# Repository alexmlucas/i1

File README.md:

# i1
An accessible motion based guitar instrument

This project is part of PhD Research being undertaken by Queens University Belfast. 

i1 is a bespoke instrument designed for and with a musician with a physical disability. The intial concept is for the musician to use head and arm movement to trigger playback of chords on a virtual guitar.

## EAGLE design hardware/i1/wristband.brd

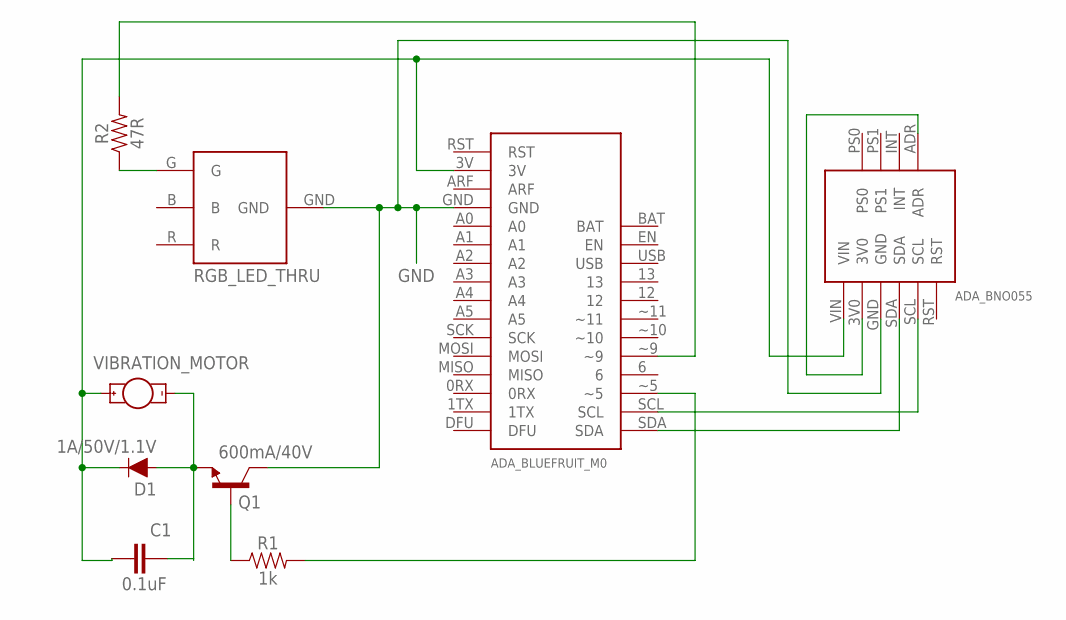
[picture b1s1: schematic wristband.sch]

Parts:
BF1: ADA_BLUEFRUIT_M0
BNO1: ADA_BNO055
C1: 0.1uF; CAP-PTH-SMALL-KIT
D1: 1A/50V/1.1V; DIODE-1N4001
Q1: 600mA/40V; TO-92
R1: 1k; AXIAL-0.3
R2: 47R; AXIAL-0.3
RGB_LED1: RGB_LED_THRU; RGB_LEB_RGB_2
U$1: VIBRATION_MOTOR

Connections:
GND: BF1.GND, BNO1.GND, Q1.1 (C), RGB_LED1.GND
unnamed: BF1.SDA, BNO1.SDA
unnamed: BF1.SCL, BNO1.SCL
unnamed: BF1.3V, BNO1.VIN, C1.1, D1.C, U$1.+
unnamed: BNO1.3V0, BNO1.ADR
unnamed: R2.P$1 (1), RGB_LED1.G
unnamed: BF1.~9, R2.P$2 (2)
unnamed: C1.2, D1.A, Q1.3 (E), U$1.-
unnamed: Q1.2 (B), R1.P$1 (1)
unnamed: BF1.~5, R1.P$2 (2)

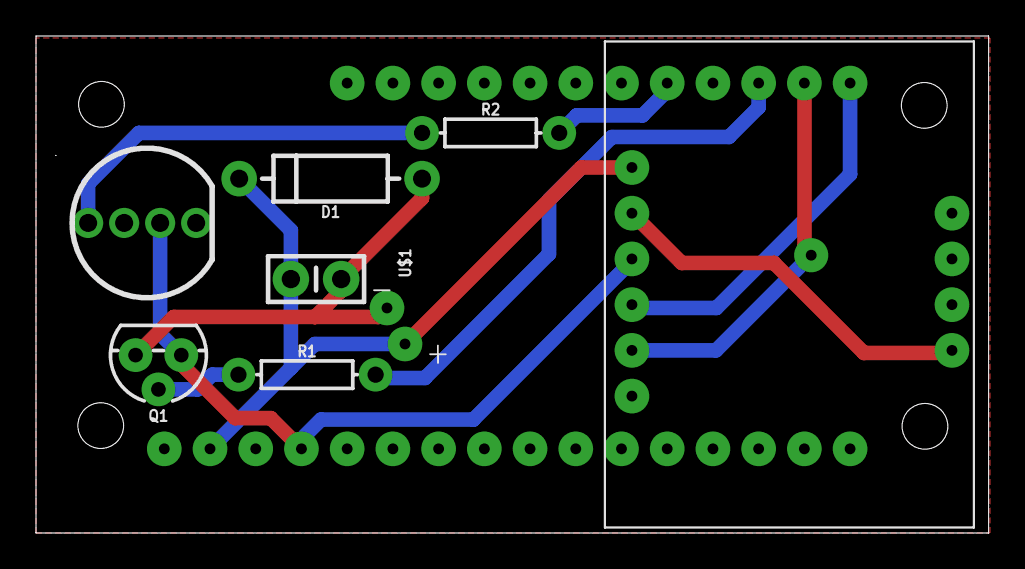
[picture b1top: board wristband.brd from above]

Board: 2 copper layers, 52.9 x 27.6 mm, 9 parts (0 on the bottom side), 10 nets.

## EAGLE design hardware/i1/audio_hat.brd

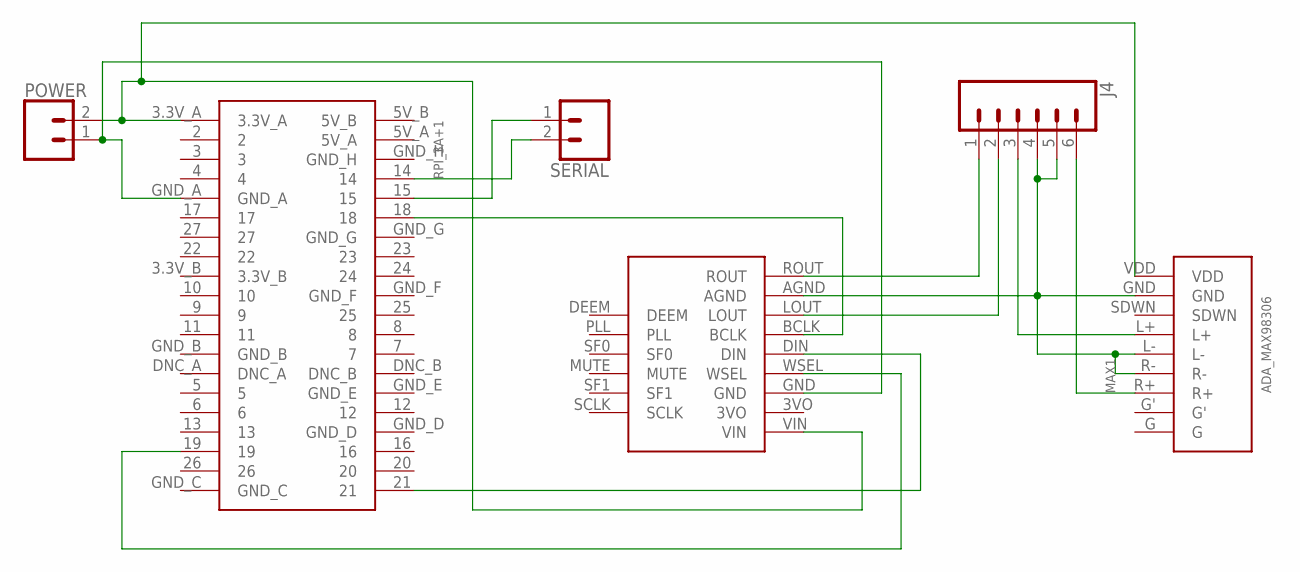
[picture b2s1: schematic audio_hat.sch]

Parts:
J4: CONN_06NO_SILK_NO_POP; 1X06_NO_SILK
MAX1: ADA_MAX98306
POWER: CONN_02; 1X02
RPI_3A+1: RPI_3A+
SERIAL: CONN_02; 1X02
UDA1: ADA_UDA1334

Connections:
unnamed: RPI_3A+1.19, UDA1.WSEL
unnamed: POWER.1, RPI_3A+1.GND_A, UDA1.GND
unnamed: MAX1.VDD, POWER.2, RPI_3A+1.3.3V_A, UDA1.VIN
unnamed: RPI_3A+1.21, UDA1.DIN
unnamed: J4.1, UDA1.ROUT
unnamed: J4.2, UDA1.LOUT
unnamed: J4.4, J4.5, MAX1.GND, MAX1.L-, MAX1.R-, UDA1.AGND
unnamed: J4.3, MAX1.L+
unnamed: RPI_3A+1.14, SERIAL.2
unnamed: J4.6, MAX1.R+
unnamed: RPI_3A+1.15, SERIAL.1
unnamed: RPI_3A+1.18, UDA1.BCLK

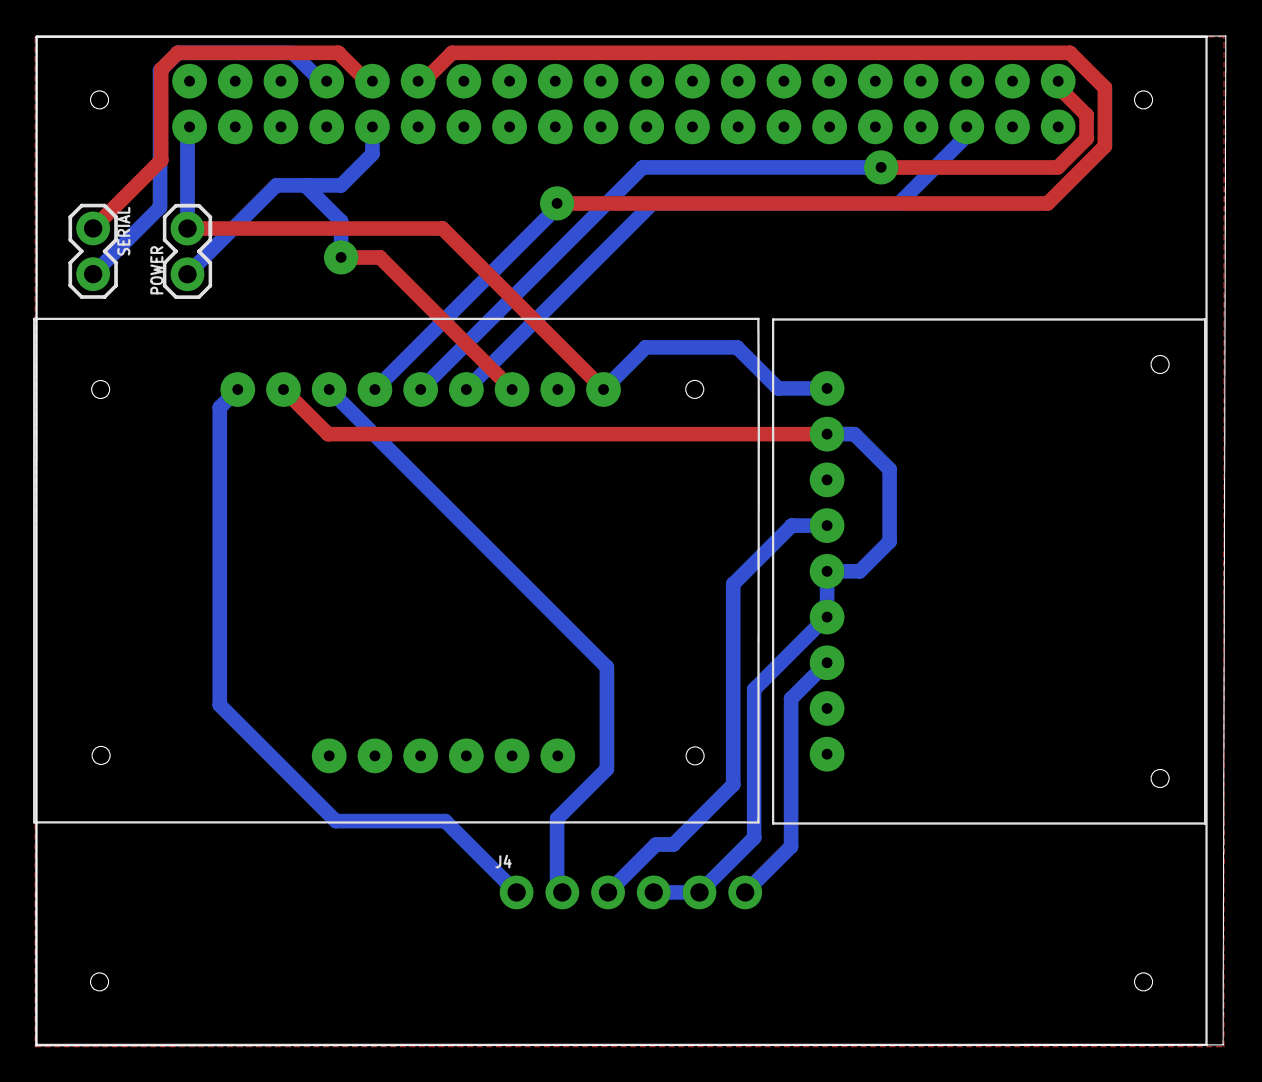
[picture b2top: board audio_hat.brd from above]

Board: 2 copper layers, 66.1 x 56.1 mm, 6 parts (0 on the bottom side), 12 nets.

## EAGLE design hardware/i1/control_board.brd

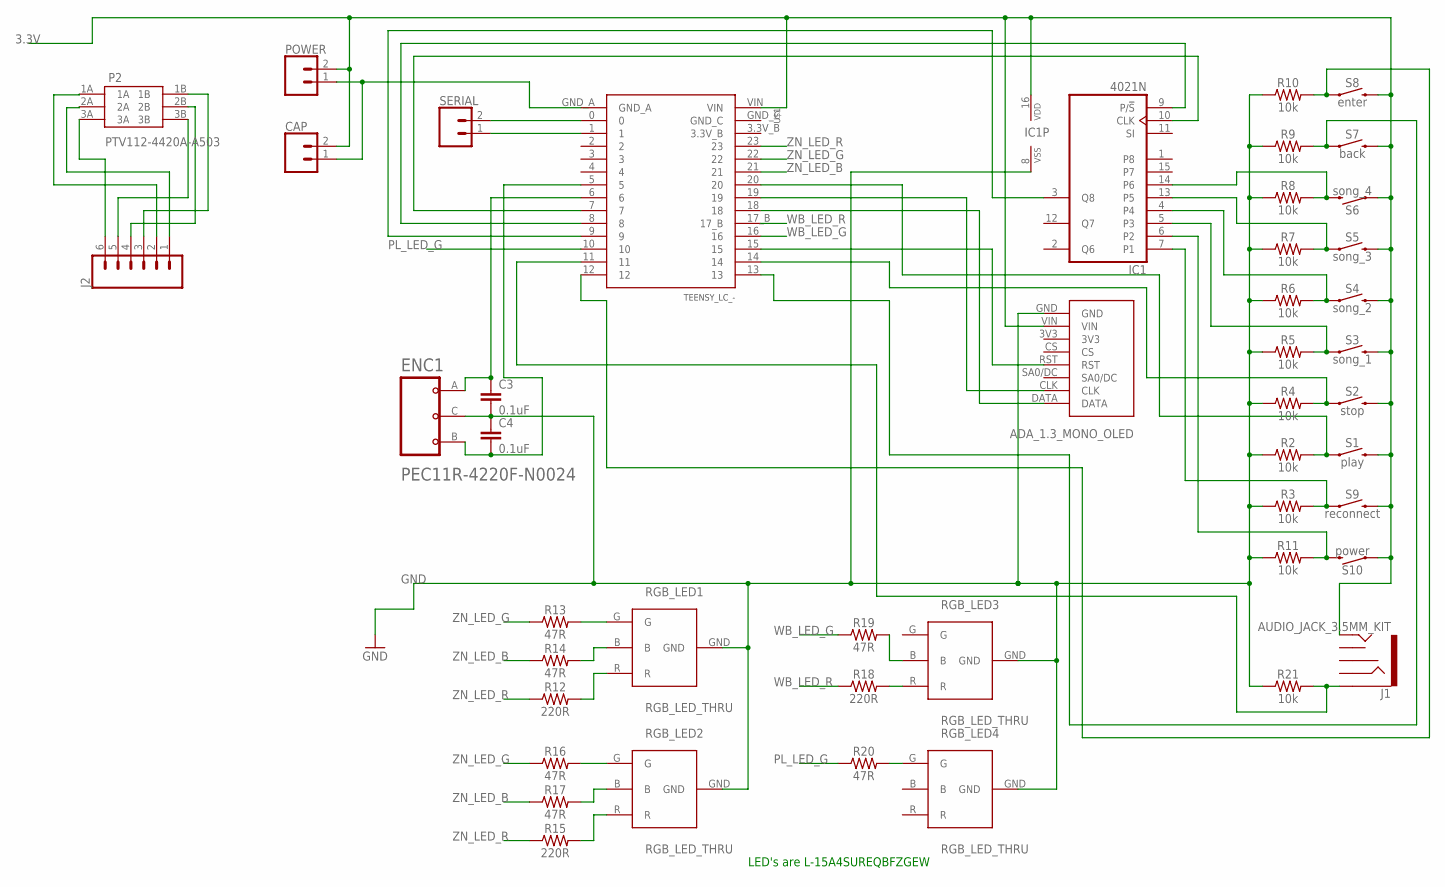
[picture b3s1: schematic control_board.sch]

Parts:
C3, C4: 0.1uF; CAP-PTH-SMALL-KIT
CAP: CONN_02; 1X02
ENC1: PEC11R-4220F-N0024
IC1: 4021N; DIL16
J1: AUDIO_JACK_3.5MM_KIT; AUDIO-JACK-KIT
J2: CONN_06NO_SILK_NO_POP; 1X06_NO_SILK
OLED1: ADA_1.3_MONO_OLED
P2: PTV112-4420A-A503; PTV122-4420A-A503
POWER: CONN_02; 1X02
R2, R3, R4, R5, R6, R7, R8, R9, R10, R11, R21: 10k; AXIAL-0.3
R12, R15, R18: 220R; AXIAL-0.3
R13, R14, R16, R17, R19, R20: 47R; AXIAL-0.3
RGB_LED1, RGB_LED2, RGB_LED3, RGB_LED4: RGB_LED_THRU; RGB_LEB_RGB_2
S1: play; TACTILE_SWITCH_PTH_6.0MM
S2: stop; TACTILE_SWITCH_PTH_6.0MM
S3: song_1; TACTILE_SWITCH_PTH_6.0MM
S4: song_2; TACTILE_SWITCH_PTH_6.0MM
S5: song_3; TACTILE_SWITCH_PTH_6.0MM
S6: song_4; TACTILE_SWITCH_PTH_6.0MM
S7: back; TACTILE_SWITCH_PTH_6.0MM
S8: enter; TACTILE_SWITCH_PTH_6.0MM
S9: reconnect; TACTILE_SWITCH_PTH_6.0MM
S10: power; TACTILE_SWITCH_PTH_6.0MM
SERIAL: CONN_02; 1X02
U$1: TEENSY_LC_-

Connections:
3.3V: CAP.2, IC1.16 (VDD), J1.TIP, OLED1.VIN, POWER.2, S1.3 (2), S2.3 (2), S3.3 (2), S4.3 (2), S5.3 (2), S6.1, S7.3 (2), S8.3 (2), S9.3 (2), S10.1, U$1.VIN
GND: C3.2, C4.1, CAP.1, ENC1.C (COMMON), IC1.8 (VSS), OLED1.GND, POWER.1, R2.P$1 (1), R3.P$1 (1), R4.P$1 (1), R5.P$1 (1), R6.P$1 (1), R7.P$1 (1), R8.P$1 (1), R9.P$1 (1), R10.P$1 (1), R11.P$1 (1), R21.P$1 (1), RGB_LED1.GND, RGB_LED2.GND, RGB_LED3.GND, RGB_LED4.GND, U$1.GND_A
unnamed: IC1.3 (Q8), U$1.9
unnamed: R13.P$2 (2), RGB_LED1.G
unnamed: R14.P$2 (2), RGB_LED1.B
unnamed: IC1.10 (CLK), U$1.7
unnamed: R12.P$2 (2), RGB_LED1.R
unnamed: R16.P$2 (2), RGB_LED2.G
unnamed: R17.P$2 (2), RGB_LED2.B
unnamed: IC1.9 (P/!S), U$1.8
unnamed: OLED1.DATA, U$1.18
unnamed: R4.P$2 (2), S2.1, U$1.14
unnamed: R9.P$2 (2), S7.1, U$1.13
unnamed: IC1.5 (P3), R5.P$2 (2), S3.1
unnamed: IC1.4, R6.P$2 (2), S4.1
unnamed: J1.SLEEVE, R21.P$2 (2), U$1.11
unnamed: IC1.13 (P5), R7.P$2 (2), S5.1
unnamed: IC1.14 (P6), R8.P$2 (2), S6.3 (2)
unnamed: SERIAL.1, U$1.1
unnamed: R10.P$2 (2), S8.1, U$1.12
unnamed: C3.1, ENC1.A (CHANNEL_A), U$1.6
unnamed: C4.2, ENC1.B (COMMON_B), U$1.5
unnamed: IC1.7 (P1), R3.P$2 (2), S9.1
unnamed: IC1.6 (P2), R11.P$2 (2), S10.3 (2)
unnamed: R15.P$2 (2), RGB_LED2.R
unnamed: R19.P$2 (2), RGB_LED3.B
unnamed: R18.P$2 (2), RGB_LED3.R
unnamed: R20.P$2 (2), RGB_LED4.G
unnamed: R2.P$2 (2), S1.1, U$1.20
unnamed: SERIAL.2, U$1.0
unnamed: J2.2, P2.1A
unnamed: OLED1.CLK, U$1.19
unnamed: OLED1.RST, U$1.15
unnamed: J2.1, P2.2A
unnamed: J2.6, P2.3A
unnamed: J2.4, P2.2B
unnamed: J2.5, P2.3B
unnamed: J2.3, P2.1B
PL_LED_G: R20.P$1 (1), U$1.10
WB_LED_G: R19.P$1 (1), U$1.16
WB_LED_R: R18.P$1 (1), U$1.17_B
ZN_LED_B: R14.P$1 (1), R17.P$1 (1), U$1.21
ZN_LED_G: R13.P$1 (1), R16.P$1 (1), U$1.22
ZN_LED_R: R12.P$1 (1), R15.P$1 (1), U$1.23

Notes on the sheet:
LED's are L-15A4SUREQBFZGEW

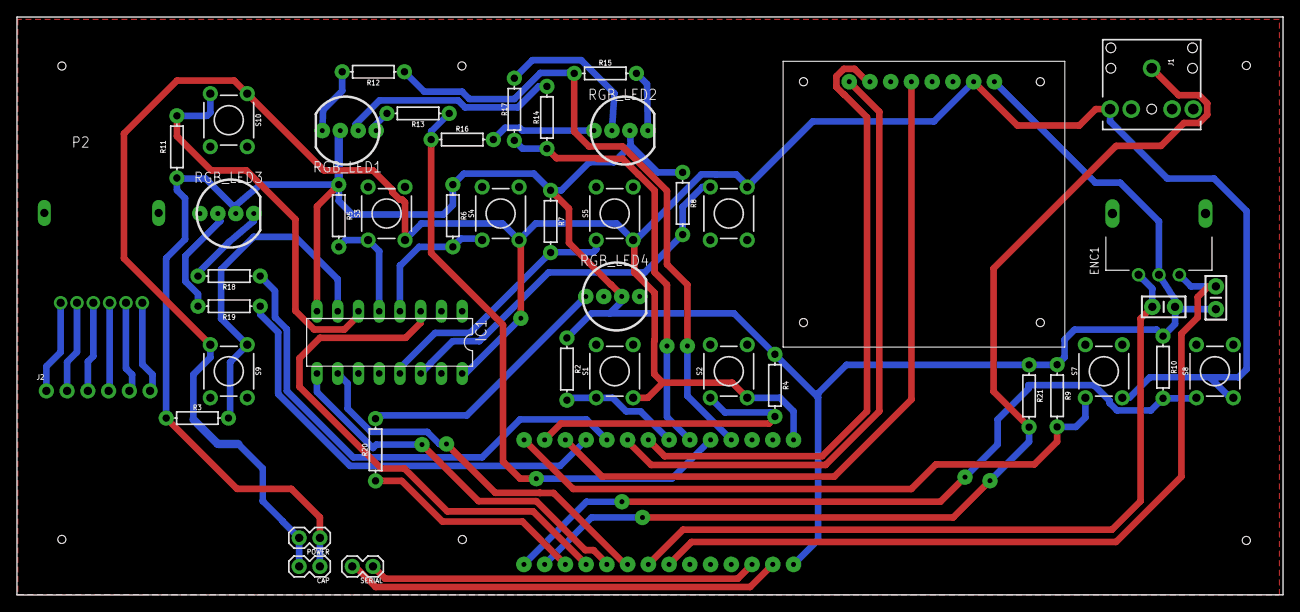
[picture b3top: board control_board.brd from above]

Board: 2 copper layers, 155.0 x 70.8 mm, 46 parts (1 on the bottom side), 44 nets.

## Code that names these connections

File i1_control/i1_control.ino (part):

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#define SHIFT_REG_CLOCK 7

// Define LED pins
#define ZN_LED_R A9
#define ZN_LED_G A8
#define ZN_LED_B A7
#define WB_LED_R A3
#define WB_LED_G A2
#define PL_LED_G 10

// Define play button states
#define PLAYING 0
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Shift_Register_Menu_Button enter_button(ENTER_BTN_BIT, DEBOUNCE_TIME, &menu_controller);

// *** Create Led instances ***
int zone_led_pins[] = {ZN_LED_R, ZN_LED_G, ZN_LED_B};
int wristband_led_pins[] = {WB_LED_R, WB_LED_G};

int RG_RED[] = {255, 0};
int RG_GREEN[] = {0, 255};
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  blue_root_menu.set_previous_menu(&red_zone_menu);
  
  // *** Configure the LEDs ***
  play_led.set_pinout(PL_LED_G);
  wristband_leds.set_pinout(wristband_led_pins);
  zone_leds.set_pinout(zone_led_pins);

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
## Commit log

2018-11-19 First commit based on initial exploratory work
2018-11-20 code relating to serial communication has been updated to allow consistent readings of two IMU's
2018-11-21 Refactored Segmenter class
    Segmenter class now has a dynamic number of segments which is determined when an instance of the class is created.
2018-11-26 First commit headset sensor
2018-11-26 Deleting due to incorrect file name
2018-11-26 First commit of headset sensor code with correct file name
2018-11-26 First commit of wristband sensor code
2018-11-28 First commit of headset 3D model
    Fusion 360 file format
2018-11-28 First commit of headset 3D model
    IGES file, which is hopefully compatible with Free Cad
2018-12-20 Fixed string trigger bug
    It wasn't possible to re-trigger a string on the outer extremities of the chord. As a result of the fix for this bug the Segmenter class has been split into two, StringSegementer and ChordSegementer.
2018-12-20 Reliability improvements
    Also removed display code and replaced with LED lighting code
2018-12-20 Incorrect file name
2018-12-20 Reliability improvements
    Also replaced display code with code for LED lighting.
2018-12-20 Reliability improvements
2019-01-29 Update main.py
    Removed headset IMU, replaced with sip/puff switch. Added bluetooth support.
2019-01-29 Changed microcontroller
    The microcontroller has been changed to an Adafruit Bluefruit M0. Bluetooth is now implemented in part.
2019-01-30 Added Adafruit Bluefruit LE Library
    Refactoring to used UART over bluetooth
2019-01-30 Refactored code based on suggestions from PyCharm
2019-01-30 adding pycharm specific files
2019-01-30 restructured files
2019-01-31 Now communicating with wristband via Bluetooth UART.
2019-01-31 Bluetooth UART implemented
    Allows triggering of motor too!
2019-01-31 Display how long each loop takes to execute.
2019-01-31 Reverted to using Bluetooth characteristics for comms
2019-01-31 Adding code for sip sensor
    An arduino sketch.
2019-01-31 Remove headset model
    No longer required.
2019-01-31 Remove headset model
    No longer required
2019-01-31 Remove headset code
    No longer required
2019-01-31 remove puff code
2019-02-04 Latest version after Friday's test
2019-03-08 Add exporatory files
2019-03-08 Added a clunky data structure for menu system
2019-03-11 Restructure menu code, improves readability
2019-03-12 Create Menu_Controller class
    To encapsulate the menu structure position
2019-03-13 Implement encoder functionality
2019-03-14 Implement Value_Page
2019-04-01 Implement menu subclasses
2019-04-11 First attempt at arduino control scanning
2019-04-17 Implement pointers in menu_page class
2019-04-17 Pass 2d char array to Menu_Page class
2019-04-17 First commit of control board schematic
2019-04-17 Commit original control board schematic as .pdf
2019-04-18 Add Parameter_Container and expand Menu_Controller
2019-04-19 Implement menu hierarchy, develop Button
    Gave Menu_Page pointer to subpages - this is how the menu hierarchy will be built.
    Enter button can now call the on_enter() function of the currently selected Menu_Page
2019-04-19 Change Menu_Page inheritance hierarchy
    Main_Page also implemented.
2019-04-20 Upload all new files.
    Value page now displays value.
    Removed unnecessary pointers.
2019-04-20 Add arduino sketch folder
2019-04-20 Call on_encoder() method from encoder class
2019-04-20 Update parameter value string on Value_Page
2019-04-20 Implemented Splash_Page
2019-04-20 Menu_Pages to have # of items member
2019-04-20 Build menu system, tidy code
2019-04-21 Fix array out of bounds bug
    Also refactored Menu Page classes to simplofy initialisation.
2019-04-21 Refactored button classes.
    Serial messages now sent from control buttons.
2019-04-21 Add LED lighting through Serial comms.
2019-04-23 Control Button aware of its parameter
2019-04-23 Refresh display when song button is pressed.
2019-04-23 New version of buttons sending serial msg
2019-04-24 Add Single_Led class
2019-04-24 Use Teensy LC rather than ATMEGA328
2019-04-24 Change LED resistor values.
    helps keep LEDs lit at a consistent brightness.
2019-04-24 Send LED lighting messages from RPi
2019-04-25 Implement inheritance in LED class
2019-04-25 Control Buttons own led pointer
2019-04-26 Fix stop button not switching off play led
2019-04-26 Fix crash on zone led set colour
2019-04-26 Control menu and wristband LEDs via serial
2019-04-26 Splash page only shown for a fixed amount of time.
2019-04-26 Reset cursor position on page change
2019-04-26 Respond to all song parameters
2019-04-26 Send song data to Teensy when requested
2019-04-26 Write Serial data from Teensy to text file
2019-04-27 Two way serial comms with character arrays of three characters
2019-04-27 Request song data in setup()
2019-04-27 Placeholder python functions for serial events
2019-04-27 Light LEDs based on intial parameter values
2019-05-02 Transfer to RPi
2019-05-02 Respond to song parameter, fix serial reading bug
2019-05-09 implement self contained guitar object
2019-05-09 read selected zone from parameter txt
2019-05-09 play songs from main script
2019-05-11 update play state and switch off play led when song changed
2019-05-12 Remove used font
2019-05-12 Remove unnecessary hidden DS file
2019-05-12 Delete Bluefruit library.
    Will be made clear that this is still a dependency.
2019-05-12 Tidy up; delete unnecessary files
2019-05-12 Test commit from Rpi
2019-05-12 updating rpi inline with local version
2019-05-12 set level of guitar, backing and master
2019-05-15 Fix bug; level didn't change with song selection
2019-05-15 Fix junk incoming serial messages
    Added a slight delay between reading each byte. Perhaps a slower BAUD rate would be better?
2019-05-15 Fix load soundfont
2019-05-18 Act on scale/chord and root messages for each zone
2019-05-18 Update scale/chord and root strings
2019-05-18 only send note off if last note
2019-05-19 Fix bug, menu not chaging after wristband connection
2019-05-19 act on serial request to reconnect wristband
2019-05-20 fix bug multiple subscriptions to yaw characteristic
2019-05-21 transmit serial on wristband reconnection
2019-05-25 test commit from patchbox os
2019-07-22 Update control_surface.ino
    Change button configuration
2019-07-23 First commit of Eagle hardware files
2019-07-24 Split into two boards
    Separate RPi audio hat
2019-07-25 Correct via routing on top layer
2019-07-30 Re-space controls - add mounting holes for RPi
    Add audio hat
2019-08-14 Audio hat now makes use of PCB via rivets
2019-08-26 Add wristband schematic and board layout
2019-08-26 Implement USB MIDI
2019-08-26 serial to request usb midi transmission
2019-08-29 transport respond to no song loaded and song end
2019-08-30 Teensy respond correctly to transport messages.
2019-08-30 implement guitar soundfonts
2019-08-30 Tighten components to allow for mounting holes
2019-08-30 Change pad size of LEDs
2019-08-30 Light LED on power
2019-09-06 pause transport bug
2019-09-08 Final tweaks for mechanical fit.
2019-09-09 Change song fail message, fix zone previous menu bug
2019-09-09 Reduce brightness of power LED
2019-09-09 fix incorrect note bug
2019-09-09 Initial commit of mechanical design
2019-09-12 add USB automount script

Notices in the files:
parts and their libraries:
SparkFun-Aesthetics: Licensing: Creative Commons ShareAlike 4.0 International - https://creativecommons.org/licenses/by-sa/4.0
SparkFun-Aesthetics: Released under the Creative Commons Attribution Share-Alike 4.0 License
SparkFun-Aesthetics: https://creativecommons.org/licenses/by-sa/4.0
